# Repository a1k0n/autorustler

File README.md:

autorustler
===========

My work-in-progress self-driving RC car.

Most host code runs on a Raspberry Pi; some runs on an Atmel AVR connected to
it via SPI.

To build on a host with a raspberry pi cross-compiler (mine's called
arm-none-linux-gnueabi-gcc, you may need to edit crosscompile.cmake):

    mkdir build
    cd build
    cmake -DCMAKE_TOOLCHAIN_FILE=../crosscompile.cmake ..
    make -j4

Building on a raspberry pi is more straightforward but slow.

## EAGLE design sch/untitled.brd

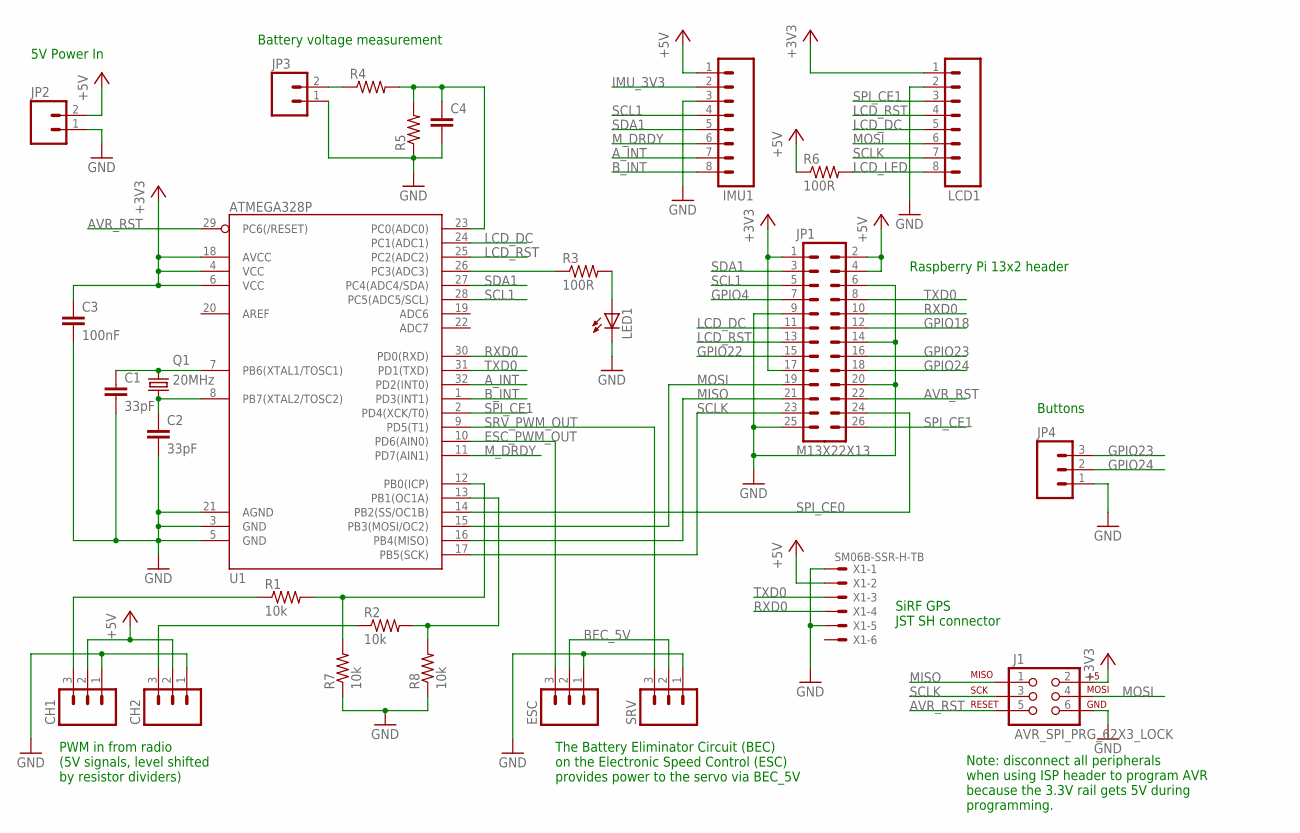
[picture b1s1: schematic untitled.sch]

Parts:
C1, C2: 33pF; 0805
C3: 100nF; 0805
C4: CAP0805; 0805
CH1, CH2: M03LOCK; 1X03_LOCK
ESC: M03LOCK; 1X03_LOCK
IMU1: M08LOCK; 1X08_LOCK
J1: AVR_SPI_PRG_62X3_LOCK; 2X3_LOCK
JP1: M13X22X13; 2X13
JP2, JP3: M02POLAR_LOCK; MOLEX-1X2_LOCK
JP4: M03POLAR_LOCK; MOLEX-1X3_LOCK
LCD1: M08LOCK; 1X08_LOCK
LED1: LED3MM
Q1: 20MHz; SM49
R1, R2, R7, R8: 10k; 0805
R3, R6: 100R; 0805
R4, R5: RESISTOR0805-RES; 0805
SRV: M03LOCK; 1X03_LOCK
U1: ATMEGA328P; TQFP32-08
X1: SM06B-SSR-H-TB

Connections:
+3V3: C3.1, J1.2, JP1.1, JP1.17, LCD1.1, U1.4 (VCC), U1.6 (VCC), U1.18 (AVCC)
+5V: CH1.2, CH2.2, IMU1.1, JP1.2, JP1.4, JP2.2, R6.1, X1.2
AVR_RST: J1.5, JP1.22, U1.29 (PC6(/RESET))
A_INT: IMU1.7, U1.32 (PD2(INT0))
BEC_5V: ESC.2, SRV.2
B_INT: IMU1.8, U1.1 (PD3(INT1))
ESC_PWM_OUT: ESC.3, U1.10 (PD6(AIN0))
GND: C1.2, C2.2, C3.2, C4.2, CH1.1, CH2.1, ESC.1, IMU1.3, J1.6, JP1.6, JP1.9, JP1.14, JP1.20, JP1.25, JP2.1, JP3.1, JP4.1, LCD1.2, LED1.K (C), R5.1, R7.1, R8.1, SRV.1, U1.3 (GND), U1.5 (GND), U1.21 (AGND), X1.1, X1.5
GPIO4: JP1.7
GPIO18: JP1.12
GPIO22: JP1.15
GPIO23: JP1.16, JP4.3
GPIO24: JP1.18, JP4.2
IMU_3V3: IMU1.2
LCD_DC: JP1.11, LCD1.5, U1.24 (PC1(ADC1))
LCD_LED: LCD1.8, R6.2
LCD_RST: JP1.13, LCD1.4, U1.25 (PC2(ADC2))
MISO: J1.1, JP1.21, U1.16 (PB4(MISO))
MOSI: J1.4, JP1.19, LCD1.6, U1.15 (PB3(MOSI/OC2))
M_DRDY: IMU1.6, U1.11 (PD7(AIN1))
unnamed: C1.1, Q1.1, U1.7 (PB6(XTAL1/TOSC1))
unnamed: C2.1, Q1.2, U1.8 (PB7(XTAL2/TOSC2))
unnamed: R3.1, U1.26 (PC3(ADC3))
unnamed: R1.2, R7.2, U1.12 (PB0(ICP))
unnamed: R2.2, R8.2, U1.13 (PB1(OC1A))
unnamed: CH1.3, R1.1
unnamed: CH2.3, R2.1
unnamed: LED1.A, R3.2
unnamed: JP3.2, R4.1
unnamed: C4.1, R4.2, R5.2, U1.23 (PC0(ADC0))
RXD0: JP1.10, U1.30 (PD0(RXD)), X1.4
SCL1: IMU1.4, JP1.5, U1.28 (PC5(ADC5/SCL))
SCLK: J1.3, JP1.23, LCD1.7, U1.17 (PB5(SCK))
SDA1: IMU1.5, JP1.3, U1.27 (PC4(ADC4/SDA))
SPI_CE0: JP1.24, U1.14 (PB2(SS/OC1B))
SPI_CE1: JP1.26, LCD1.3, U1.2 (PD4(XCK/T0))
SRV_PWM_OUT: SRV.3, U1.9 (PD5(T1))
TXD0: JP1.8, U1.31 (PD1(TXD)), X1.3

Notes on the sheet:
The Battery Eliminator Circuit (BEC) on the Electronic Speed Control (ESC) provides power to the servo via BEC_5V
PWM in from radio (5V signals, level shifted by resistor dividers)
5V Power In
Battery voltage measurement
SiRF GPS JST SH connector
Note: disconnect all peripherals when using ISP header to program AVR because the 3.3V rail gets 5V during programming.
Raspberry Pi 13x2 header
Buttons

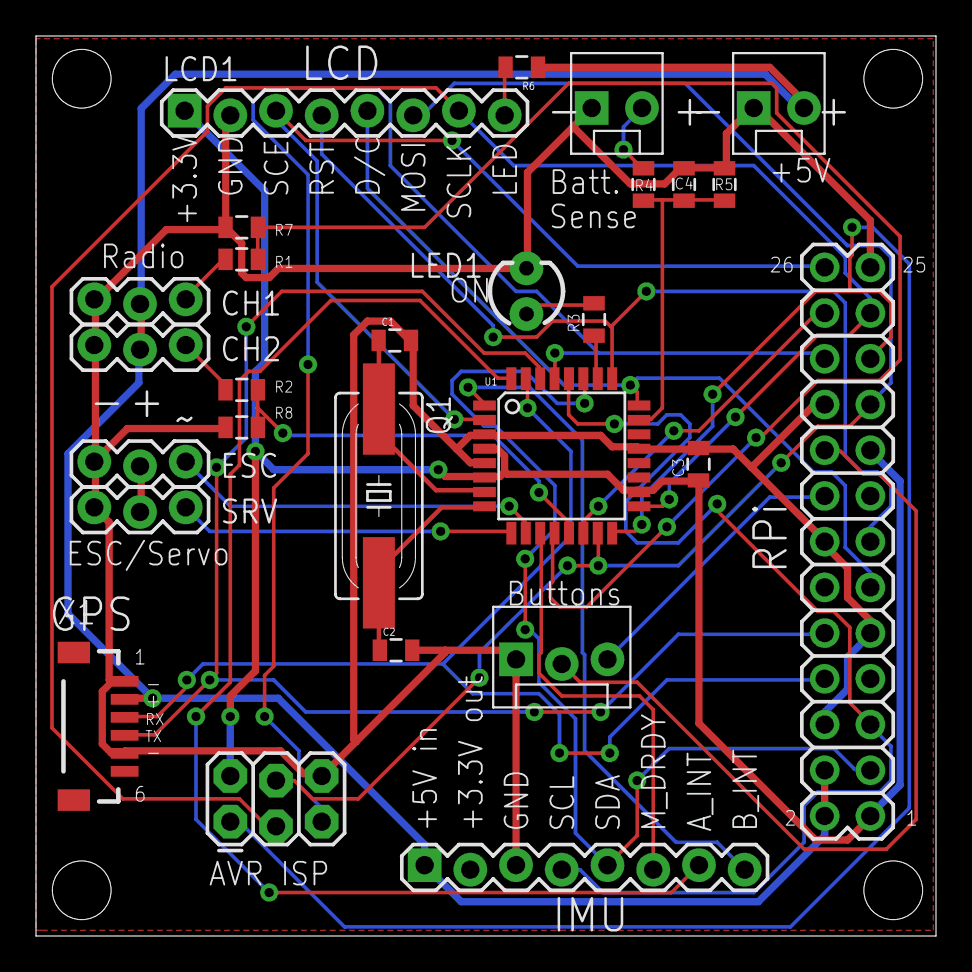
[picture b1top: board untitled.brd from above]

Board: 2 copper layers, 50.0 x 50.0 mm, 27 parts (0 on the bottom side), 34 nets.

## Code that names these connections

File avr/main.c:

#include <avr/interrupt.h>
#include <avr/io.h>
#include <avr/pgmspace.h>
#include <avr/wdt.h>
#include <util/delay.h>

static uint16_t battery_voltage = 0;

volatile static uint8_t ch1_counts = 0, ch2_counts = 0;
volatile static uint8_t pwm_mirror = 1;
ISR(PCINT0_vect) {
  static uint8_t ch1_start = 0, ch2_start = 0;
  static uint8_t ch1_state = 0, ch2_state = 0;
  uint8_t tm = TCNT0;
  uint8_t state = PINB;
  if ((state&1) != ch1_state) {
    ch1_state = state&1;
    if (ch1_state) {
      ch1_start = tm;
    } else {
      ch1_counts = (tm - ch1_start);
    }
  }
  if ((state&2) != ch2_state) {
    ch2_state = state&2;
    if (ch2_state) {
      ch2_start = tm;
    } else {
      ch2_counts = (tm - ch1_start);
    }
  }
}

// dumb int-on-pin-change pwm capture
static void pwmcapture_init() {
  PORTB = 0x03;  // add pull-ups to inputs
  PCMSK0 = 0x03;
  PCICR = 0x01;
}

ISR(SPI_STC_vect) {
  uint8_t spi_in = SPDR;
  static uint8_t spi_state = 0, spi_hibyte = 0;
  static uint8_t spi_readlen = 0;
  switch (spi_state) {
    default:  // command mode, state 0 (or invalid states)
      if (spi_in == 0x01) {  // command 0x01: read timer
        SPDR = TCNT1L;
        spi_hibyte = TCNT1H;
        spi_state = 1;
      } else if (spi_in == 0x02) {  // command 0x02: read PWM input state
        SPDR = ch1_counts;
        spi_hibyte = ch2_counts;
        spi_state = 1;
      } else if (spi_in == 0x03) {  // command 0x03: set pwm mirroring
        SPDR = 1 + (pwm_mirror << 1);
        spi_state = 5;
      } else if (spi_in == 0x04) {  // command 0x04: set pwm output
        SPDR = 1;
        spi_state = 6;
      } else if (spi_in == 0x05) {  // command 0x05: get battery voltage
        SPDR = battery_voltage & 0xff;
        spi_hibyte = battery_voltage >> 8;
        spi_state = 1;
      } else {  // unknown command, or padding (command 0)
        SPDR = 0;
      }
      break;
    case 1: // send one high byte, then return to state 0
      SPDR = spi_hibyte;
      spi_state = 0;
      break;
    case 5: // set PWM mirror
      pwm_mirror = spi_in;
      SPDR = 0;
      spi_state = 0;
      break;
    case 6: // set PWM output ch1
      SPDR = OCR0A;
      OCR0A = spi_in;
      spi_state++;
      break;
    case 7: // set PWM output ch2
      SPDR = OCR0B;
      OCR0B = spi_in;
      spi_state = 0;
      break;
  }
}

static void spi_init() {
  // PB3 (MOSI), PB5 (SCK), PB2 (/SS) input
  // PB4 (MISO) output
  DDRB |= 0x10;
  // enable SPI
  SPCR = (1<<SPE) | (1<<SPIE);
}

static void pwmgen_init() {
  // Generate PWM on PD6/PD5 (OC0A/OC0B respectively)
  // ugh, this is only 8-bit PWM, though, and at ~300Hz.  i hope that
  // works.
  // set TMR0 prescaler to /256
  DDRD |= (1<<5) | (1<<6);

  // period in ms = 65536/F_CPU
  // duration of N counts (milliseconds) = T = 256000*n/F_CPU
  // n = T*F_CPU/256000
  OCR0A = (1.5*F_CPU/256000);
  OCR0B = (1.5*F_CPU/256000);
  // (at 20MHz this gives a dynamic range of 78-156, 117 being center)
  // so ~6.3 bit pwm...

  TCCR0A = 0xA3; // enable OC0A, OC0B, fast PWM mode
  TCCR0B = 0x04; // prescaler /256, 305.1Hz (3.2768ms cycle)
}

int main() {
  // enable WDT
  wdt_enable(WDTO_15MS);

  // Set up TMR1 to count up on each clock cycle (20MHz)
  TCCR1B = 0x01;

  // set up ADC on channel 0
  PORTC = 0;
  DDRC = 1<<3;
  DIDR0 = 0x01;
  ADMUX = 0xc0;  // internal 1.1V ref, select ADC0
  ADCSRA = 0x87;  // enable ADC

  spi_init();
  pwmcapture_init();
  pwmgen_init();

  sei();

  uint32_t itercount = 0;
  for (;;) {
    itercount++;
    wdt_reset();
    if (!(itercount&0x7ffff)) {
      PORTC ^= 1<<3;
      ADCSRA |= _BV(ADSC);
      while(!bit_is_set(ADCSRA,ADIF));
      ADCSRA |= _BV(ADIF);
      battery_voltage = ADC;
    }
    if (pwm_mirror && ch1_counts != 0 && ch2_counts != 0) {
      OCR0A = ch1_counts;
      OCR0B = ch2_counts;
    }
  }
}

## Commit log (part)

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2013-12-04 Blinking LED on outboard atmega328p. woo.
2013-12-04 SPI hello world woo
2013-12-05 read 16-bit 20MHz timer via SPI
2013-12-06 Read 2-channel PWM input, make it available on SPI
    I can't believe I got this to work with such small jitter. It bounces
    around by about 10-15 counts but is usually pretty dead-on. I might do
    a histogram and add an input filter.
    Something is a little funky electrically: it only works if pullups are
    enabled, which leads me to believe either the radio is open collector or
    its output impedance is pretty high. Nevertheless, with my 10k/10k
2013-12-07 PWM output; mirroring input pulse duration
    but it's pretty ugly; only ~6 bits of precision. Which is probably
    plenty for the application, actually.
2013-12-09 8-bit pwm capture queue via SPI
    uses only 8-bit TMR0 for capture as that's also what's used for
    generation. can probably optimize some more now.
2013-12-09 don't blink the LED so fast.
2013-12-10 Organize code
2013-12-11 clean up the code a bit, use text UBX init message
2013-12-11 smarter NMEA message generator
    there's a bug in the UBX binary protocol receiver somewhere... random
    input bytes are being discarded, and i don't think it's baudrate related
2013-12-12 Fixed bad checksum read errors from GPS.
    Turns out the serial port had friggin' XON/XOFF flow control, so a 0x11
    appearing in binary data would be silently dropped! ARGH!
    Also, when first enabling the UART transmitter on the RPi, it glitches a
    start bit, so if you immediately start sending you get a framing error
    (thanks, logic analyzer! I never would have noticed otherwise...).
    Added a 1ms delay and a spurious \r\n\r\n.
2013-12-26 battery sense wire
    this seems a bit too noisy right now; not sure what the deal is
2013-12-26 use ECEF coords in binary protocol
2013-12-30 WIP ECEF conversions, local reference plane
2014-03-08 ECEF fixes
2014-03-09 Adding i2c IMU code
2014-03-10 accelerometer reading + notes
2014-03-16 make i2c-imu a library
2014-03-16 ubx: fix on-boot init
    basically, try *really hard* not to mess up the serial port, and close
    and reopen it after we change baud rates.
2014-03-16 rename ubx -> gps
2014-03-16 refactoring gps code
2014-03-17 motion model notes
2014-03-23 new GPS module support: SiRF
2014-03-23 SiRF message parsing
2014-03-30 adjustments to IMU bandwidth/samplerates
2014-03-30 function to send SiRF messages (not yet used)
2014-03-30 imu: output pretty printing, sync to system clock @ 50Hz
2014-03-31 SiRF: send DGPS enable message
    this doesn't seem to work, though, as I'm not getting any response
    messages
2014-03-31 imu: better poll timing
2014-04-14 adding EAGLE schematic + pcb
2014-04-14 Better PCB annotations, moved stuff and re-routed
2014-04-14 critical PCB connector fixes
    - flipped RPi connector around to correct orientation
    - flipped SiRF GPS connector around
    - added two more resistors to radio input, so there's a resistor
    divider instead of relying on overload protection
    - powered LCD backlight LED by 5v instead of 3.3v, resistor can adjust
    brightness
2014-04-30 Some AVR changes to accomodate new circuit board
2014-04-30 LCD/SPI refactoring & cleanup
    (N.B. I broke it with this commit, need to debug)
2014-04-30 fix lcd init bugs, add more interesting test
2014-04-30 LCD: add text drawing, fix contrast
2014-04-30 avr: brown-out detect + watchdog
2014-05-01 add radio reading code to UI
    also a little cleaning up
2014-05-02 Add battery voltage measurement
2014-05-04 add imu + input logger
    (need to add gps support to the logger also)
    also swapped steering/throttle; i must have had it backwards before
2014-08-23 raise magnetometer sample rate, fix radio input glitch
2014-08-23 add userland submodule
2014-08-23 Build raspi userland stuff w/ cmake
2014-09-07 added cam/: capture raspicam images
    stripped essentials out of RaspiCamYUV to make it work
2014-09-07 README
2014-09-07 switch to my fork of userland until merge
2014-09-07 fix messed up branch pointer
2014-09-07 take video at 10fps
2014-09-07 Stripped extra junk out of cam code
    also added a dumb script to show I420 YUV frames captured by the camera
2014-09-07 remove even more unnecessary crap
2014-09-07 significantly clean up cam stuff
2014-09-07 Add missing cross-compiler definition
2014-09-07 Cpplint style cleanup
    run with: cpplint.py --filter=-legal *.cc *.h */*.cc */*.h
2014-09-07 camtest: ^C to stop recording
2014-09-08 Don't use gcc extensions for initializing camera structures
2014-09-08 forgot the gps subdir in CMakeLists.txt
2014-09-10 Added OpenCV FAST keypoint detector to vis
2014-09-10 linux fixes
2014-09-10 use FAST-9 directly
2014-09-10 use find_package for OpenCV
2014-09-10 camera/vis: support stdin/stdout streaming
2014-09-11 vis: 640x480 window, camera calibration experiment
2014-09-27 ui: read buttons
2014-09-27 camtest: specify fps on cmdline
    also played with buffering stuff but we still drop frames
2014-09-27 simplified the radio code, made it more robust
2014-09-28 only update steering/throttle input state if valid
2014-09-28 fix startup servo glitch
2014-09-28 reorg tree
2014-09-28 new UI which captures camera, imu, gps, buttons
    the dithered display is buggy right now, need to fix (and gamma-correct)
2014-09-28 minor ui stuff, 8x8 dither matrix
2014-09-28 much better LCD status indicators
2014-09-29 more improved sensor reporting on LCD
2014-10-14 push button to record!
2014-10-14 drop root privs once we no longer need them
2014-10-14 meh, use a 16-byte header
2014-10-14 magnetometer/gyro calibration tests
2014-10-14 convert to Eigen
2014-10-14 better method, but man, my offsets are awful
    gotta move the sensor, i think
2014-10-14 trying to do tilt compensation, probably wrong
2014-10-15 temperature-calibrated gyro input
2014-10-16 this kalman filter doesn't work at all
    there's a much simpler way to do this, coming next
    http://www.freescale.com/files/sensors/doc/app_note/AN4246.pdf
2014-10-16 this least-squares solution works much better
    however, correlated inputs mess it up; maybe we can de-weight each
    sample based on informativeness (like, 1-dot product)
2014-10-16 weight calibration samples by cosine distance from previous
2014-10-20 Added online calibration and reorganized some stuff
2014-10-20 vis: read new log format
2014-10-20 more indicators
2014-10-22 begin design of enclosure for all hardware
    just roughing out dimensions here relative to battery holder widget
2014-10-22 roughing in an rpi
2014-10-23 more accurate rpi
2014-10-23 better mounting thingies
2014-10-23 manufacturability tweaks
2014-10-23 thinner walls, reinforcing ridges
2014-10-25 fix minor recording bugs
2014-10-25 add simple record log parser
2014-10-30 feature point tracking across frames
    still pretty buggy, needs lots of tuning
    also i can draw lines now, yay
2015-09-19 WIP: monocular SLAM tests in numpy
2015-09-19 i must have forgotten to add tracktest.cc
2015-09-24 finally corrected the gradient computations
2015-10-10 just... playing around with stuff
2015-10-17 playing with calibration
2015-10-17 several fixes after 1st print
    - lengthened entire part by 1mm
    - overbored all holes by .02" / 0.5mm to compensate for nozzle diameter
    / material infill
    - made bosses considerably thicker so they can be machined (maybe?)
    - moved camera mount into a separate part which mates with the existing
    screws
2015-10-17 parametric camera holder thingy
2015-10-17 I wrote all this months ago and have no idea what any of it is anymore
2015-10-17 Moved camera mount flush with front
    now it can be 3d printed without weird support issues
2015-10-17 convert all to metric, clean up code and remove old junk
2015-10-17 more traxxas parts
2015-10-17 update baseplate
2015-12-19 forgot to add fasteners.scad
2016-01-08 some python IMU stuff
2016-01-08 redoing raspberry pi + battery + camera mounts
2016-01-08 readme in scad/
2017-02-01 just updating compiler, userland
2017-02-20 a bunch of work in progress
    switching from janky usb-serial microcontroller to PCA9685 servo
    control, bluetooth controller input instead of PWM sampling
    switching to MPU9250 instead of three-device frankenstein
    also discovered some bad math but not the correct math
2017-02-20 use new i2c class for IMU
2017-02-20 add untested joystick input code
2017-02-24 add some test programs, drive with bluetooth controller
2017-02-25 support button input
2017-02-25 code to drive and record camera input
2017-03-22 DIYRobocars track parameterized
2017-03-25 initial wip
2017-03-25 i can't believe this actually worked
2017-03-26 code to undistort/rectify
2017-03-26 camera calibration junk
2017-03-27 just use fisheye with K1 distortion...
    anything else is just nuts
2017-04-01 various experiments which seem to help
    nearly able to localize with a particle filter, I think...
2017-04-09 dumb simulator in curvilinear space
    next: find optimal theoretical controller
2017-04-11 fix simulation step update in curvilinear space
2017-05-11 make the camera holder taller
    can't 3d print anything bigger than this
2017-05-14 ported EKF to C++/Eigen
    TODO: PID drive code
2017-05-14 disable mag cal for now; update filters and gyro range
2017-05-14 make mpu9150 imu code actually work
2017-05-14 neat PID controller. overshoots the turn, but simple.
2017-05-14 add save thread, IMU to driver
2017-05-14 final form of EKF
2017-05-14 run #3 code
2017-05-14 clean up drive controller code; add undistorted regression
2017-05-14 code for run #2
    forgot to commit run #1
2017-05-14 an EKF that actually works!!!!!!
    it's able to determine the car's velocity and the track curvature
    through the interplay of control inputs, gyro reading, and linear
    regression of the detected yellow center markers.
2017-05-14 blah jupyter junk
2017-05-14 FINALLY, a dialed-in PD controller.
    On the full size track I can reduce P a bit and raise the traction
    limit (in the driveway I get lost and crash).
2017-05-14 another error in the control law, this one minor
    sin^2 psi times curvature was negative, but that's a pretty small
    correction (usually).
2017-05-17 this thing *FLIES* now with ESC out of traing mode
    had to reduce the throttle limit until it learns about braking and
    lateral dynamics...
2017-05-21 made a new circuit board tray thing
2017-06-15 racing line optimizer
    saved out a racing line relative to centerline markings; combined with
    particle filter localization, should be able to drive along racing line
    and beat the course in ~9 seconds
2017-06-16 updated simulator + driver code
    - loads properly (meter-) scaled track
    - PD steering as before but drives on precomputed racing line
    - rethought throttle control; velocity based on curvature, braking
    based on curvature lookahead
2017-06-16 assorted updates
2017-06-16 make sim.py state consistent w/ robot car state
    psi / w were backwards wrt the car
    now we have a corrected control law
2017-07-07 experiments in fine-grained motor control
2017-07-09 refinements to camera holders
    plus a new one for the arducam form factor.
2017-07-09 adjust lens hole center
2017-07-15 new EKF, new controls, new imgproc pipeline
2017-07-16 teensy lib fixes
2017-07-17 YESSS, IT FINALLY WORKS AGAIN!
2017-08-10 use autogenerated EKF code. fingers crossed.
2017-08-10 holy stupid bugs batman!
    this thing finally runs correctly!!!!!!!!1
2017-08-11 3.4m/s speed limit, awesome run Thu 8/10/2017
2017-08-11 oops, bug in motor control math
2017-08-12 fix bug w/ motor control, average all moving encoders
    (and don't apply wheel encoder update at all if none are moving)
2017-08-12 smooth as butter now. awesome.
    still might need some process noise tuning, still need to figure out
    what's wrong with the IMU updates, it still might get lost if it
    completely loses the line...
    but this is pretty badass now.
2017-08-17 back on track with fixed EKF model
2017-08-17 more bugs! more tuning!
    there's something wrong with motor control; that's what i need to fix
    next. it's overshooting turns, and i have to raise P and D to keep it
    tight but it oscillates too much now.
2017-08-19 brake more aggressively; esp. when steering is maxed out
2017-08-20 hairpin powersliding! woo!
2017-08-20 updated teensy code & 3d models
2017-08-20 this repo is such a huge mess
2017-08-20 remove dead code

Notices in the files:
parts and their libraries:
SparkFun-DigitalIC: Licensing: CC v3.0 Share-Alike You are welcome to use this library for commercial purposes.
